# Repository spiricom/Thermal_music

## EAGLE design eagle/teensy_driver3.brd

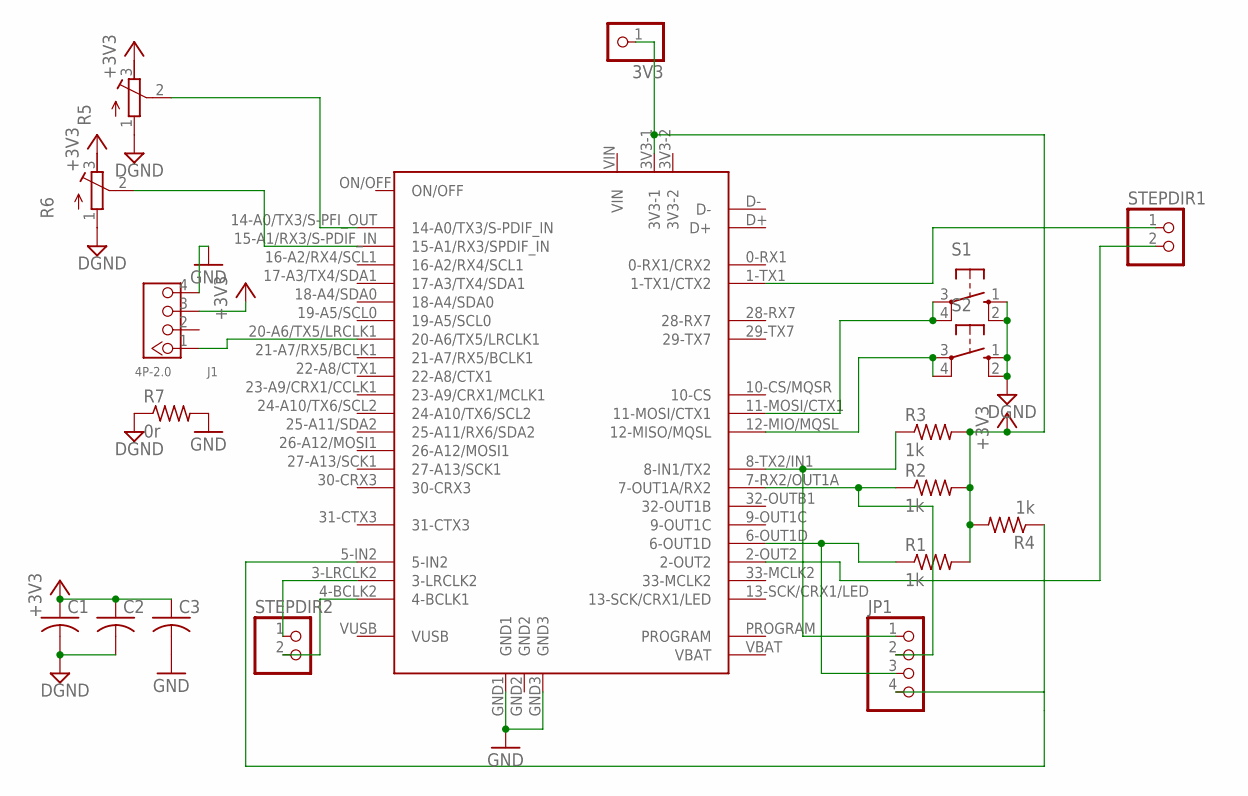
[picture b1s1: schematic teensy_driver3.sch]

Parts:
3V3: PINHD-1X1; 1X01
C1, C2, C3: C-US025_050-055X075; C025_050-055X075
J1: 4P-2.0; HW4-2.0
JP1: PINHD-1X4; 1X04
R1, R2, R3, R4: 1k; 0207/7
R5, R6: R-TRIMM74X; RTRIM74X
R7: 0r; 0204/7
S1, S2: 10-XX; B3F-10XX
STEPDIR1, STEPDIR2: PINHD-1X2; 1X02
U$1: TEENSY40

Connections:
+3V3: 3V3.1, C1.1, C2.1, C3.1, J1.3, R1.2, R2.2, R3.2, R4.2, R5.3 (E), R6.3 (E), U$1.3V3-1
DGND: C1.2, C2.2, R5.1 (A), R6.1 (A), R7.1, S1.1 (S), S1.2 (S1), S2.1 (S), S2.2 (S1)
GND: C3.2, J1.4, R7.2, U$1.GND1, U$1.GND3
unnamed: JP1.3, R1.1, U$1.6-OUT1D
unnamed: JP1.2, R2.1, U$1.7-RX2/OUT1A (7-OUT1A/RX2)
unnamed: JP1.1, R3.1, U$1.8-TX2/IN1 (8-IN1/TX2)
unnamed: JP1.4, R4.1, U$1.5-IN2
unnamed: STEPDIR1.2, U$1.2-OUT2
unnamed: STEPDIR1.1, U$1.1-TX1 (1-TX1/CTX2)
unnamed: STEPDIR2.1, U$1.3-LRCLK2
unnamed: STEPDIR2.2, U$1.4-BCLK2 (4-BCLK1)
unnamed: J1.1, U$1.20-A6/TX5/LRCLK1
unnamed: R5.2 (S), U$1.14-A0/TX3/S-PFI_OUT (14-A0/TX3/S-PDIF_IN)
unnamed: R6.2 (S), U$1.15-A1/RX3/S-PDIF_IN (15-A1/RX3/SPDIF_IN)
unnamed: S1.3, S1.4 (P1), U$1.11-MOSI/CTX1
unnamed: S2.3, S2.4 (P1), U$1.12-MIO/MQSL (12-MISO/MQSL)

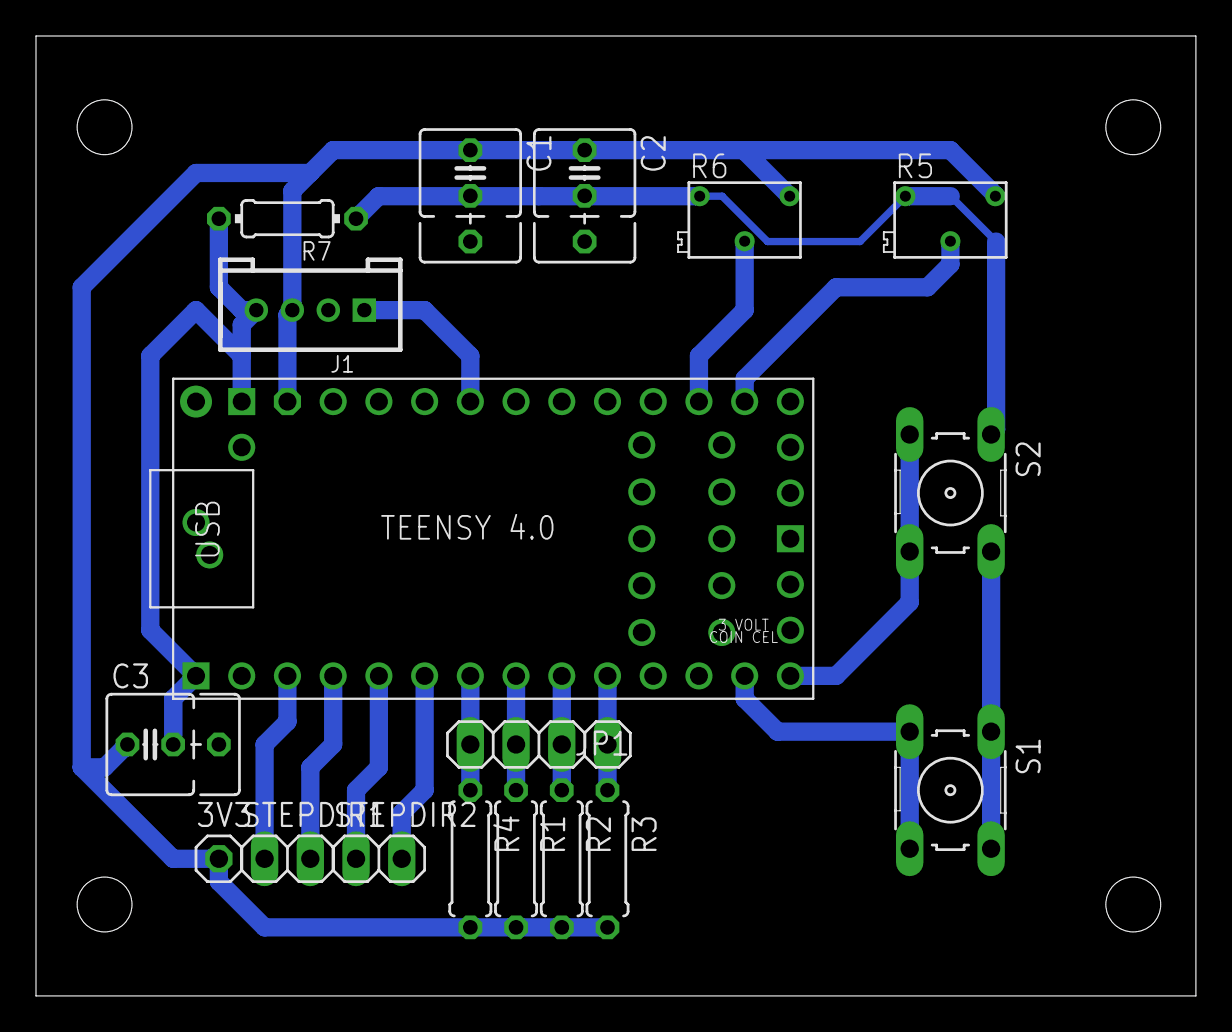
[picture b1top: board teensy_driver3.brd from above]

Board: 2 copper layers, 64.4 x 53.3 mm, 18 parts (0 on the bottom side), 16 nets.

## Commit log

2023-09-29 startin it up dudez
2023-09-29 Add README and git ignore
2023-09-29 Adding CustomerSpeedStepp
2023-09-30 added custom speed stepper library
2023-10-06 added DMX control
2023-10-13 fix floating point error
2023-10-13 add controller max patch
2023-10-24 newest version
2023-10-26 tools for thermal music
2023-10-27 sped up maximum speed a bit and changed factors for acceleration and speed
2023-10-27 changed names and improved light code
